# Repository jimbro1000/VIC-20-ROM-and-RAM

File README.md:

# VIC-20 Internal ROM Replacement and RAM Expansion #

This repository contains the design for a PCB to replace the
basic and kernel ROMs in a Commodore VIC-20. As a bonus the
board can also carry up to 32K of RAM to expand the memory
capacity internally without the need for RAM expansion 
cartridges.

## ROM Replacement

The board is designed to use 27c64 EPROMs to replace the
two core masked ROMs. It is expected to replace both - 
although it is possible to replace just one and will 
work with only one and it doesn't matter which, although
it is far more likely that it will be the kernel ROM
as these seem to be less reliable.

Binary images for the BASIC and Kernel ROMs can be
found here: [http://www.zimmers.net/anonftp/pub/cbm/firmware/computers/vic20/](http://www.zimmers.net/anonftp/pub/cbm/firmware/computers/vic20/)

## RAM Expansion

The board has four positions for RAM ICs, it is not
necessary to fill any or all of these posiitons but
they must be populated from right to left (any
unused positions must be to the left).

### Selecting RAM Size

The board includes a bank of 4 DIP switches that can be
used to enable or disable RAM ICs. As with populating the
RAM ICs on the board the switches should be used in
descending order to reduce capacity, from left to right.

If a RAM expansion cart is to be used as well it is important
to avoid conflicts by disabling the appropriate RAM ICs.
This is even more important if the cartridge has a ROM
assigned to one of those slots.

## Assembly

The interactive BOM can be found in this repositiory:
[./bom/ibom.html](bom/ibom.html)

The trickiest part of the assembly is fitting the connecting
pins on the lower side of the board. These need to be 
accurately aligned to ensure they will fit the main board
correctly. It is recommended to use turned pin headers cut
to the right length. Once soldered in place the pins 
extending on the upper side of the board will need to be 
trimmed down to allow sockets to be fitted over them.

The rest of the board should be straight forward assembly.

For J1 (connections to the cartridge port), it is recommended
to use pin headers or a pin socket so that the board can
be removed without significant effort.

## RAM Only Expansion ##

If you *only* want to utilise the RAM expansion capability
of the board it will still need a connection to the main
board through one of the ROM positions. To do this the
original ROM must be removed but can be reattached to 
the top of the expansion board. In this situation do not
fit the socket for an EPROM and solder the original ROM
to the exposed pins connecting to the original ROM
position. This can be tricky and is best done by bending
the ROM chip legs in slightly so that they sit inside
the exposed pins on both sides, but still touching. This
should simplify the soldering task.

## Installation ##

### ROM Operation

The board is installed by soldering the pins on the 
bottom of the board into the original ROM positions of
the main board.

### RAM Operation

In addition to the connections under the board the
RAM Expansion requires additional connections to be
made. The expectation is that these will be to the
exposed pins of the cartridge port.

The expansion board has 5 pins at the top that 
need to be connected (from left to right) to
pins 18 (CRW), 13, 12, 11 and 10 (BLK5, 3, 2 and 1).
These provide the Read/Write and enable signals
to the RAM ICs, without these connections the
RAM will not operate.

The connections to the cartridge port can be
soldered to those pins or through the use of
wiring probes/clips. Soldered connections
should prove more durable but makes the install
more permanent.

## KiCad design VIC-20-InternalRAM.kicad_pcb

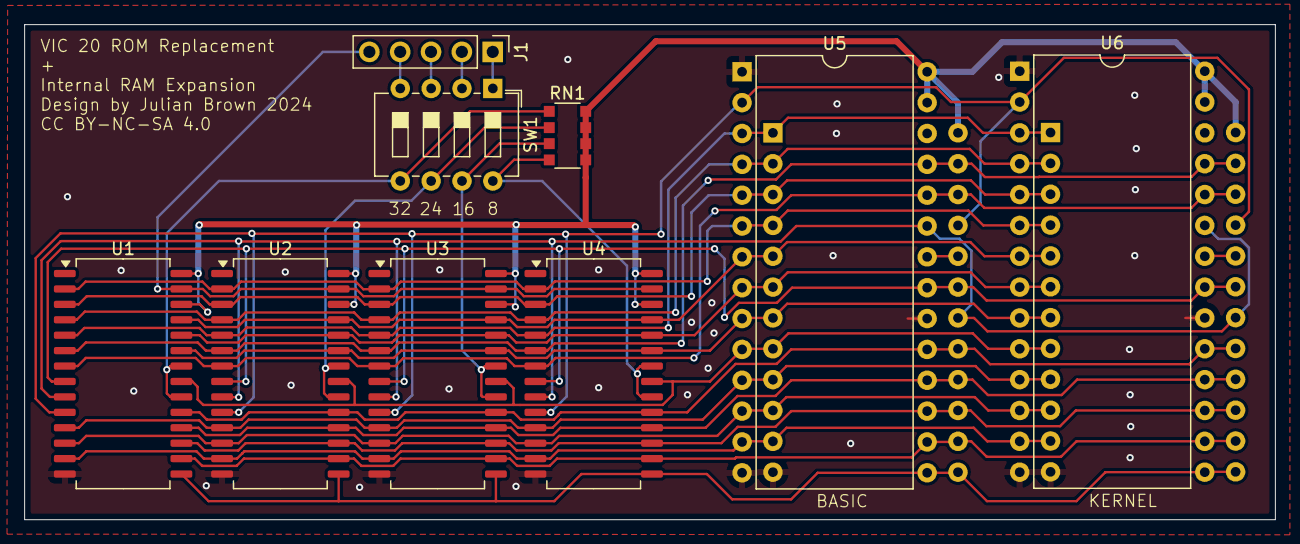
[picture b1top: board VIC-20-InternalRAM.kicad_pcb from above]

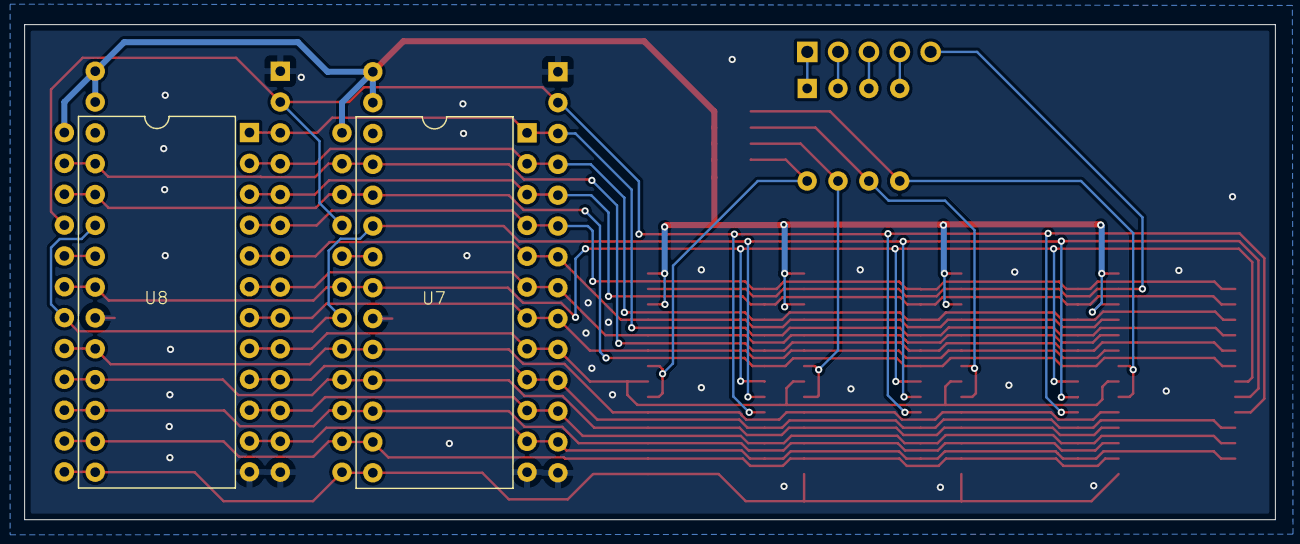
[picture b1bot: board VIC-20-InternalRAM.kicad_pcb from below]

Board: 2 copper layers, 103.0 x 40.8 mm, 11 parts (2 on the bottom side), 34 nets.

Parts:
J1: P6; PinHeader_1x05_P2.54mm_Vertical
RN1: 4K7; R_Array_Convex_4x1206
SW1: SW_DIP_x04; SW_DIP_SPSTx04_Slide_6.7x11.72mm_W7.62mm_P2.54mm_LowProfile
U1, U2, U3, U4: CY6264-70SNC; SOIC-28W_7.5x18.7mm_P1.27mm
U5: 27C64 - BASIC; DIP-28_W15.24mm
U6: 27C64 - KERNEL; DIP-28_W15.24mm
U7: BASIC; 2364
U8: KERNEL; 2364

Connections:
+5V: RN1.5 (R4.2), RN1.6 (R3.2), RN1.7 (R2.2), RN1.8 (R1.2), U1.26 (CE2), U1.28 (Vcc), U2.26 (CE2), U2.28 (Vcc), U3.26 (CE2), U3.28 (Vcc), U4.26 (CE2), U4.28 (Vcc), U5.27 (~PGM), U5.28 (VCC), U6.27 (~PGM), U6.28 (VCC), U7.24 (Vcc), U8.24 (Vcc)
/A0: U1.21 (A0), U2.21 (A0), U3.21 (A0), U4.21 (A0), U5.10 (A0), U6.10 (A0), U7.8 (A0), U8.8 (A0)
/A1: U1.23 (A1), U2.23 (A1), U3.23 (A1), U4.23 (A1), U5.9 (A1), U6.9 (A1), U7.7 (A1), U8.7 (A1)
/A2: U1.24 (A2), U2.24 (A2), U3.24 (A2), U4.24 (A2), U5.8 (A2), U6.8 (A2), U7.6 (A2), U8.6 (A2)
/A3: U1.25 (A3), U2.25 (A3), U3.25 (A3), U4.25 (A3), U5.7 (A3), U6.7 (A3), U7.5 (A3), U8.5 (A3)
/A4: U1.2 (A4), U2.2 (A4), U3.2 (A4), U4.2 (A4), U5.6 (A4), U6.6 (A4), U7.4 (A4), U8.4 (A4)
/A5: U1.3 (A5), U2.3 (A5), U3.3 (A5), U4.3 (A5), U5.5 (A5), U6.5 (A5), U7.3 (A5), U8.3 (A5)
/A6: U1.4 (A6), U2.4 (A6), U3.4 (A6), U4.4 (A6), U5.4 (A6), U6.4 (A6), U7.2 (A6), U8.2 (A6)
/A7: U1.5 (A7), U2.5 (A7), U3.5 (A7), U4.5 (A7), U5.3 (A7), U6.3 (A7), U7.1 (A7), U8.1 (A7)
/A8: U1.6 (A8), U2.6 (A8), U3.6 (A8), U4.6 (A8), U5.25 (A8), U6.25 (A8), U7.23 (A8), U8.23 (A8)
/A9: U1.7 (A9), U2.7 (A9), U3.7 (A9), U4.7 (A9), U5.24 (A9), U6.24 (A9), U7.22 (A9), U8.22 (A9)
/A10: U1.8 (A10), U2.8 (A10), U3.8 (A10), U4.8 (A10), U5.21 (A10), U6.21 (A10), U7.19 (A10), U8.19 (A10)
/A11: U1.9 (A11), U2.9 (A11), U3.9 (A11), U4.9 (A11), U5.23 (A11), U6.23 (A11), U7.18 (A11), U8.18 (A11)
/A12: U1.10 (A12), U2.10 (A12), U3.10 (A12), U4.10 (A12), U5.2 (A12), U6.2 (A12), U7.21 (A12), U8.21 (A12)
/BLK1: RN1.4 (R4.1), SW1.8, U4.20 (~CE1), U4.22 (~OE)
/BLK2: RN1.3 (R3.1), SW1.7, U3.20 (~CE1), U3.22 (~OE)
/BLK3: RN1.2 (R2.1), SW1.6, U2.20 (~CE1), U2.22 (~OE)
/BLK5: RN1.1 (R1.1), SW1.5, U1.20 (~CE1), U1.22 (~OE)
/BLK6: U5.22 (~OE), U7.20 (~E)
/BLK7: U6.22 (~OE), U8.20 (~E)
/D0: U1.11 (D0), U2.11 (D0), U3.11 (D0), U4.11 (D0), U5.11 (D0), U6.11 (D0), U7.9 (D0), U8.9 (D0)
/D1: U1.12 (D1), U2.12 (D1), U3.12 (D1), U4.12 (D1), U5.12 (D1), U6.12 (D1), U7.10 (D1), U8.10 (D1)
/D2: U1.13 (D2), U2.13 (D2), U3.13 (D2), U4.13 (D2), U5.13 (D2), U6.13 (D2), U7.11 (D2), U8.11 (D2)
/D3: U1.15 (D3), U2.15 (D3), U3.15 (D3), U4.15 (D3), U5.15 (D3), U6.15 (D3), U7.13 (D3), U8.13 (D3)
/D4: U1.16 (D4), U2.16 (D4), U3.16 (D4), U4.16 (D4), U5.16 (D4), U6.16 (D4), U7.14 (D4), U8.14 (D4)
/D5: U1.17 (D5), U2.17 (D5), U3.17 (D5), U4.17 (D5), U5.17 (D5), U6.17 (D5), U7.15 (D5), U8.15 (D5)
/D6: U1.18 (D6), U2.18 (D6), U3.18 (D6), U4.18 (D6), U5.18 (D6), U6.18 (D6), U7.16 (D6), U8.16 (D6)
/D7: U1.19 (D7), U2.19 (D7), U3.19 (D7), U4.19 (D7), U5.19 (D7), U6.19 (D7), U7.17 (D7), U8.17 (D7)
/P6p10: J1.1, SW1.1
/P6p11: J1.2, SW1.2
/P6p12: J1.3, SW1.3
/P6p13: J1.4, SW1.4
/P6p18: J1.5, U1.27 (~WE), U2.27 (~WE), U3.27 (~WE), U4.27 (~WE)
GND: U1.14 (GND), U2.14 (GND), U3.14 (GND), U4.14 (GND), U5.1 (VPP), U5.14 (GND), U5.20 (~CE), U6.1 (VPP), U6.14 (GND), U6.20 (~CE), U7.12 (GND), U8.12 (GND)

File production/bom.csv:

Designator,Footprint,Quantity,Value,LCSC Part #
J1,PinHeader_1x05_P2.54mm_Vertical,1,P6,
RN1,R_Array_Convex_4x1206,1,4K7,
SW1,SW_DIP_SPSTx04_Slide_6.7x11.72mm_W7.62mm_P2.54mm_LowProfile,1,SW_DIP_x04,
"U1, U2, U3, U4",SOIC-28W_7.5x18.7mm_P1.27mm,4,CY6264-70SNC,
U5,DIP-28_W15.24mm,1,27C64 - BASIC,
U6,DIP-28_W15.24mm,1,27C64 - KERNEL,
U7,2364,1,BASIC,
U8,2364,1,KERNEL,

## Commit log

2024-11-16 update render
2024-11-16 include production files

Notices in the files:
VIC-20-InternalRAM.kicad_pcb:
CC BY-NC-SA 4.0
